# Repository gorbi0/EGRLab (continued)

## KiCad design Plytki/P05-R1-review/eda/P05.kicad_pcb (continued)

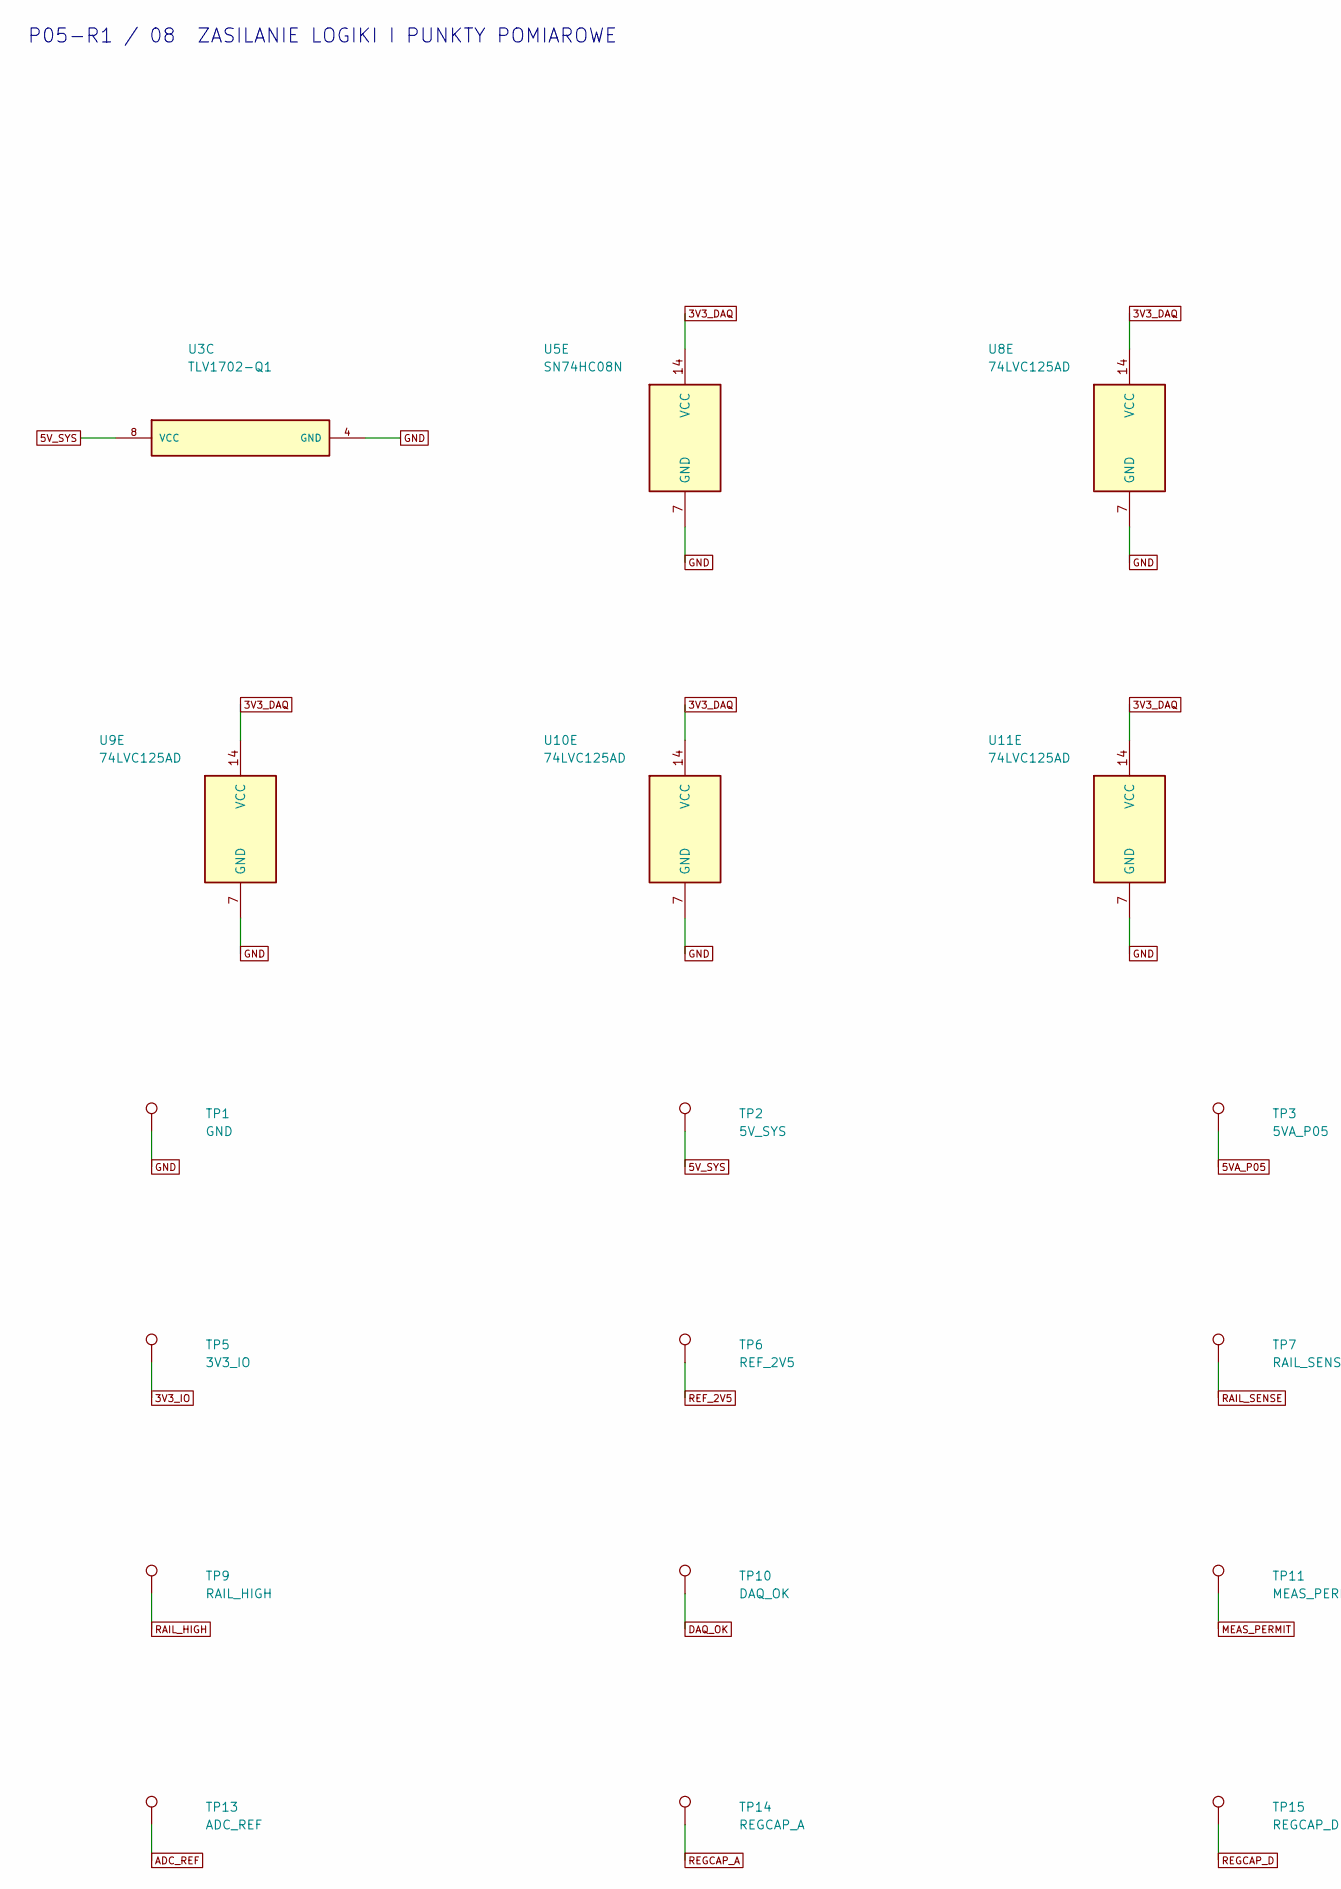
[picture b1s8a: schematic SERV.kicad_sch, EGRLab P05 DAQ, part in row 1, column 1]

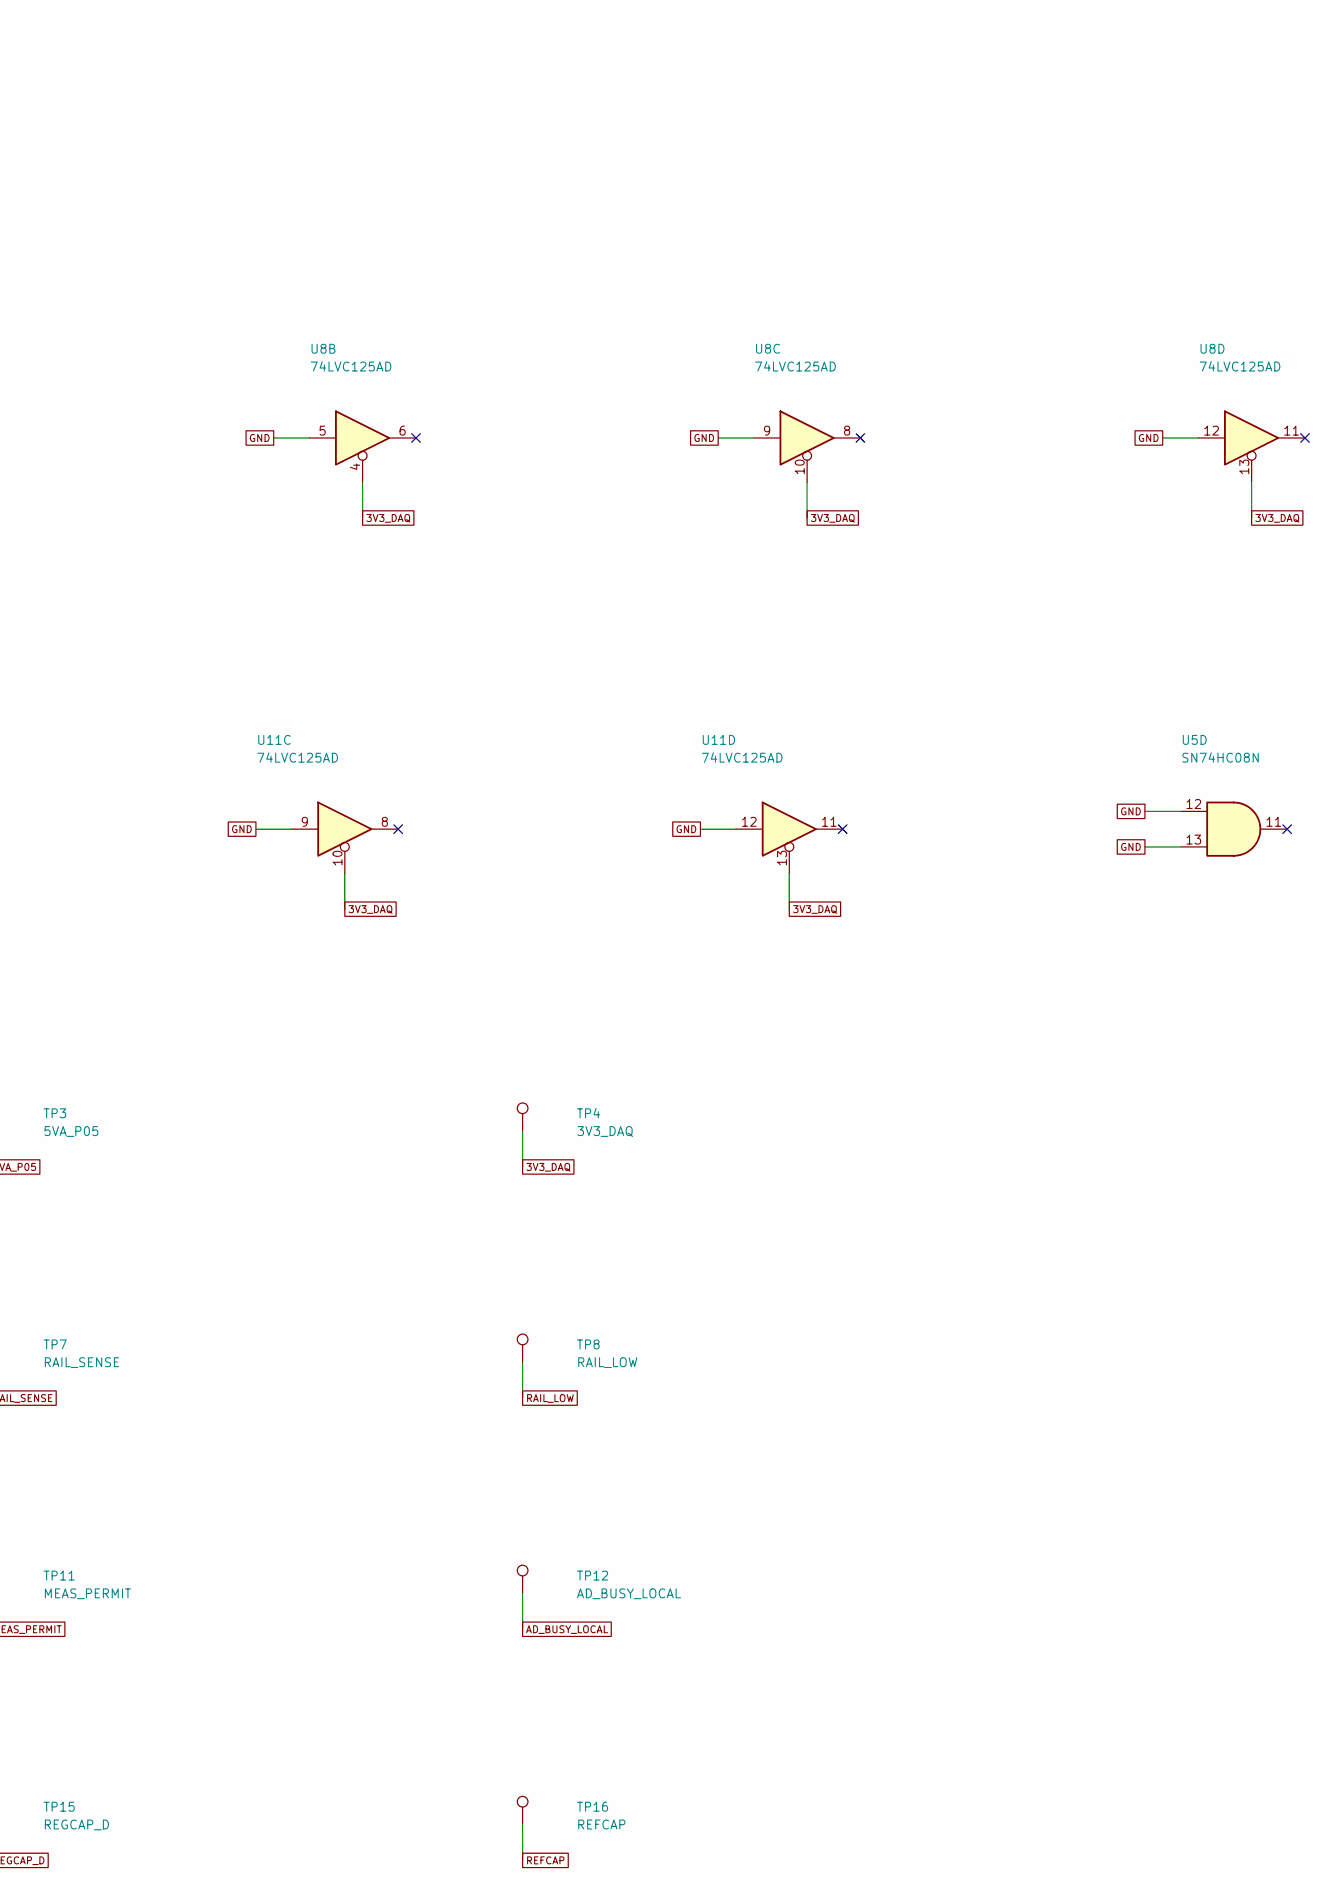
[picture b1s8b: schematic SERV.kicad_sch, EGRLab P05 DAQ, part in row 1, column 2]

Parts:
TP1: GND; TestPad_1; MPN PCB test pad
TP2: 5V_SYS; TestPad_1; MPN PCB test pad
TP3: 5VA_P05; TestPad_1; MPN PCB test pad
TP4: 3V3_DAQ; TestPad_1; MPN PCB test pad
TP5: 3V3_IO; TestPad_1; MPN PCB test pad
TP6: REF_2V5; TestPad_1; MPN PCB test pad
TP7: RAIL_SENSE; TestPad_1; MPN PCB test pad
TP8: RAIL_LOW; TestPad_1; MPN PCB test pad
TP9: RAIL_HIGH; TestPad_1; MPN PCB test pad
TP10: DAQ_OK; TestPad_1; MPN PCB test pad
TP11: MEAS_PERMIT; TestPad_1; MPN PCB test pad
TP12: AD_BUSY_LOCAL; TestPad_1; MPN PCB test pad
TP13: ADC_REF; TestPad_1; MPN PCB test pad
TP14: REGCAP_A; TestPad_1; MPN PCB test pad
TP15: REGCAP_D; TestPad_1; MPN PCB test pad
TP16: REFCAP; TestPad_1; MPN PCB test pad
U3: TLV1702-Q1; VSSOP-8_3x3mm_P0.65mm; MPN TLV1702AQDGKRQ1
U5: SN74HC08N; DIP-14_W7.62mm; MPN SN74HC08N
U8, U9, U10, U11: 74LVC125AD; SOIC-14_3.9x8.7mm_P1.27mm; MPN 74LVC125AD,118

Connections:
3V3_DAQ: TP4.1, U5.14 (VCC), U8.4, U8.10, U8.13, U8.14 (VCC), U9.14 (VCC), U10.14 (VCC), U11.10, U11.13, U11.14 (VCC); also elsewhere on the board
3V3_IO: TP5.1; also elsewhere on the board
5VA_P05: TP3.1; also elsewhere on the board
5V_SYS: TP2.1, U3.8 (VCC); also elsewhere on the board
ADC_REF: TP13.1; also elsewhere on the board
AD_BUSY_LOCAL: TP12.1; also elsewhere on the board
DAQ_OK: TP10.1; also elsewhere on the board
GND: TP1.1, U3.4 (GND), U5.7 (GND), U5.12, U5.13, U8.5, U8.7 (GND), U8.9, U8.12, U9.7 (GND), U10.7 (GND), U11.7 (GND), U11.9, U11.12; also elsewhere on the board
MEAS_PERMIT: TP11.1; also elsewhere on the board
RAIL_HIGH: TP9.1; also elsewhere on the board
RAIL_LOW: TP8.1; also elsewhere on the board
RAIL_SENSE: TP7.1; also elsewhere on the board
REFCAP: TP16.1; also elsewhere on the board
REF_2V5: TP6.1; also elsewhere on the board
REGCAP_A: TP14.1; also elsewhere on the board
REGCAP_D: TP15.1; also elsewhere on the board

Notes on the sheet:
P05-R1 / 08 ZASILANIE LOGIKI I PUNKTY POMIAROWE

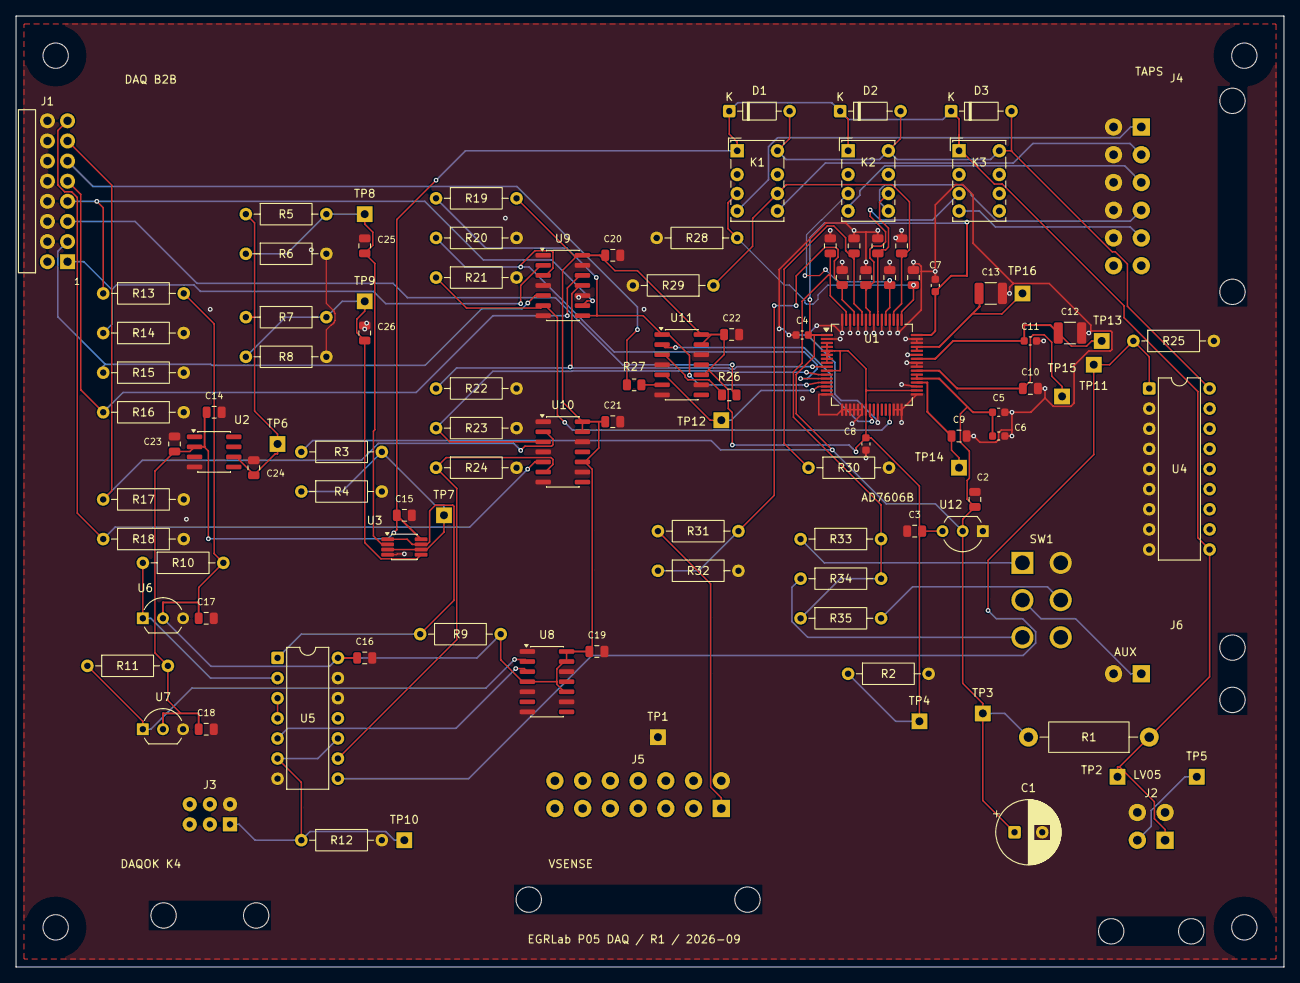
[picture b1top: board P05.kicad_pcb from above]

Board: 2 copper layers, 160.0 x 120.0 mm, 114 parts (0 on the bottom side), 57 nets.

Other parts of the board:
H1, H2, H3, H4: M3 NPTH

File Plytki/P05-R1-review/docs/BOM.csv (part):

ref;source_ref;display;mpn;qty;footprint;on_board;url;note
U1;U1;AD7606BBSTZ;AD7606BBSTZ;1;Package_QFP:LQFP-64_10x10mm_P0.5mm;True;https://www.analog.com/media/en/technical-documentation/data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;"OS=111 serial software; REF_SELECT high = internal reference. Grounded DB pins per serial-mode data sheet."
U2;U13;ADR4525BRZ;ADR4525BRZ;1;Package_SO:SOIC-8_3.9x4.9mm_P1.27mm;True;https://www.analog.com/media/en/technical-documentation/data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;"Reference for rail window only; NOT ADC reference."
U3;U6;TLV1702-Q1;TLV1702AQDGKRQ1;1;Package_SO:VSSOP-8_3x3mm_P0.65mm;True;https://www.ti.com/lit/ds/symlink/tlv1702-q1.pdf;
U4;U18;TBD62083APG;TBD62083APG;1;Package_DIP:DIP-18_W7.62mm;True;https://toshiba.semicon-storage.com/us/semiconductor/product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;COM to coil supply. Inputs 2..8 tied low. Local diodes at coils.
U5;U_READY;SN74HC08N;SN74HC08N;1;Package_DIP:DIP-14_W7.62mm;True;https://www.ti.com/lit/ds/symlink/sn74hc08.pdf;
U6;U_SUP3;MCP120-300DI/TO;MCP120-300DI/TO;1;Package_TO_SOT_THT:TO-92_Inline_Wide;True;https://ww1.microchip.com/downloads/en/DeviceDoc/11184d.pdf;D bondout 1 reset, 2 VDD, 3 GND. Open drain.
U7;U_SUP5;MCP120-450DI/TO;MCP120-450DI/TO;1;Package_TO_SOT_THT:TO-92_Inline_Wide;True;https://ww1.microchip.com/downloads/en/DeviceDoc/11184d.pdf;D bondout 1 reset, 2 VDD, 3 GND. Open drain.
U8;U_SUPBUF;74LVC125AD;74LVC125AD,118;1;Package_SO:SOIC-14_3.9x8.7mm_P1.27mm;True;https://assets.nexperia.com/documents/data-sheet/74LVC125A.pdf;"Nexperia Ioff, soldered directly; no adapter."
U9;U_RX1;74LVC125AD;74LVC125AD,118;1;Package_SO:SOIC-14_3.9x8.7mm_P1.27mm;True;https://assets.nexperia.com/documents/data-sheet/74LVC125A.pdf;"Nexperia Ioff, soldered directly; no adapter."
U10;U_RX2;74LVC125AD;74LVC125AD,118;1;Package_SO:SOIC-14_3.9x8.7mm_P1.27mm;True;https://assets.nexperia.com/documents/data-sheet/74LVC125A.pdf;"Nexperia Ioff, soldered directly; no adapter."
U11;U_TX;74LVC125AD;74LVC125AD,118;1;Package_SO:SOIC-14_3.9x8.7mm_P1.27mm;True;https://assets.nexperia.com/documents/data-sheet/74LVC125A.pdf;"Nexperia Ioff, soldered directly; no adapter."
U12;ADDED_LOCAL_LDO;MCP1700-3302E/TO;MCP1700-3302E/TO;1;Package_TO_SOT_THT:TO-92_Inline_Wide;True;https://ww1.microchip.com/downloads/aemDocuments/documents/A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;Local logic supply derived from ADC AVCC. LV05.3 is test point only.
R1;R_FILT;1R;metal film resistor 1R 1%;1;Resistor_THT:R_Axial_DIN0411_L9.9mm_D3.6mm_P15.24mm_Horizontal;True;;"1W minimum; pulse energy at turn-on >=6mJ. One full-value resistor, no series substitution. Precision parts TCR <=25ppm/K."
C1;C_A;470u / 16V;EEUFR1C471;1;Capacitor_THT:CP_Radial_D8.0mm_P3.50mm;True;;"Panasonic FR, D8 x 11.5mm, pitch 3.5mm; 20%."
C2;ADDED_LDO_IN;1u;X7R 25V 10% 1u;1;Capacitor_SMD:C_0805_2012Metric;True;;
C3;ADDED_LDO_OUT;2.2u;X7R 25V 10% 2.2u;1;Capacitor_SMD:C_0805_2012Metric;True;;
R2;ADDED_LDO_BLEED;1K;metal film resistor 1K 1%;1;Resistor_THT:R_Axial_DIN0207_L6.3mm_D2.5mm_P10.16mm_Horizontal;True;;One full-value resistor, no series substitution. Precision parts TCR <=25ppm/K.
C4;C_DEC_U1_1;100n;X7R 25V 10% 100n;1;Capacitor_SMD:C_0603_1608Metric;True;;
C5;C_DEC_U1_37;100n;X7R 25V 10% 100n;1;Capacitor_SMD:C_0603_1608Metric;True;;
C6;C_DEC_U1_38;100n;X7R 25V 10% 100n;1;Capacitor_SMD:C_0603_1608Metric;True;;
C7;C_DEC_U1_48;100n;X7R 25V 10% 100n;1;Capacitor_SMD:C_0603_1608Metric;True;;
C8;C_DEC_U1_23;100n;X7R 25V 10% 100n;1;Capacitor_SMD:C_0603_1608Metric;True;;
C9;C_REGCAP_A;1u;X7R 25V 10% 1u;1;Capacitor_SMD:C_0805_2012Metric;True;;
C10;C_REGCAP_D;1u;X7R 25V 10% 1u;1;Capacitor_SMD:C_0805_2012Metric;True;;
C11;C_ADC_REF;100n;X7R 25V 10% 100n;1;Capacitor_SMD:C_0603_1608Metric;True;;
C12;ADDED_INTERNAL_REF_BULK;22u;C3225X7R1E226M250AB;1;Capacitor_SMD:C_1210_3225Metric;True;https://product.tdk.com/en/search/capacitor/ceramic/mlcc/inf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;22uF 25V X7R 20%, 1210. Ceff >=10uF including bias/tolerance/temperature: procurement acceptance, not yet measured.
C13;C_REFCAP;22u;C3225X7R1E226M250AB;1;Capacitor_SMD:C_1210_3225Metric;True;https://product.tdk.com/en/search/capacitor/ceramic/mlcc/inf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;22uF 25V X7R 20%, 1210. Ceff >=10uF including bias/tolerance/temperature: procurement acceptance, not yet measured.
C14;C_DEC_U2;100n;X7R 25V 10% 100n;1;Capacitor_SMD:C_0805_2012Metric;True;;
C15;C_DEC_U3;100n;X7R 25V 10% 100n;1;Capacitor_SMD:C_0805_2012Metric;True;;
C16;C_DEC_U5;100n;X7R 25V 10% 100n;1;Capacitor_SMD:C_0805_2012Metric;True;;
C17;C_DEC_U6;100n;X7R 25V 10% 100n;1;Capacitor_SMD:C_0805_2012Metric;True;;
C18;C_DEC_U7;100n;X7R 25V 10% 100n;1;Capacitor_SMD:C_0805_2012Metric;True;;
C19;C_DEC_U8;100n;X7R 25V 10% 100n;1;Capacitor_SMD:C_0805_2012Metric;True;;
C20;C_DEC_U9;100n;X7R 25V 10% 100n;1;Capacitor_SMD:C_0805_2012Metric;True;;
C21;C_DEC_U10;100n;X7R 25V 10% 100n;1;Capacitor_SMD:C_0805_2012Metric;True;;
C22;C_DEC_U11;100n;X7R 25V 10% 100n;1;Capacitor_SMD:C_0805_2012Metric;True;;
C23;C_REF_IN;1u;X7R 25V 10% 1u;1;Capacitor_SMD:C_0805_2012Metric;True;;
C24;C_REF_OUT;1u;X7R 25V 10% 1u;1;Capacitor_SMD:C_0805_2012Metric;True;;
C25;C_RAIL_LOW;10n;X7R 25V 10% 10n;1;Capacitor_SMD:C_0805_2012Metric;True;;
C26;C_RAIL_HIGH;10n;X7R 25V 10% 10n;1;Capacitor_SMD:C_0805_2012Metric;True;;
R3;R_RAIL_T;15K;MBB0207 precision metal film 15K 0.1%;1;Resistor_THT:R_Axial_DIN0207_L6.3mm_D2.5mm_P10.16mm_Horizontal;True;;One full-value resistor, no series substitution. Precision parts TCR <=25ppm/K.
R4;R_RAIL_B;10K;MBB0207 precision metal film 10K 0.1%;1;Resistor_THT:R_Axial_DIN0207_L6.3mm_D2.5mm_P10.16mm_Horizontal;True;;One full-value resistor, no series substitution. Precision parts TCR <=25ppm/K.
R5;R_RAIL_LT;5.90K;MBB0207 precision metal film 5.90K 0.1%;1;Resistor_THT:R_Axial_DIN0207_L6.3mm_D2.5mm_P10.16mm_Horizontal;True;;One full-value resistor, no series substitution. Precision parts TCR <=25ppm/K.
R6;R_RAIL_LB;20K;MBB0207 precision metal film 20K 0.1%;1;Resistor_THT:R_Axial_DIN0207_L6.3mm_D2.5mm_P10.16mm_Horizontal;True;;One full-value resistor, no series substitution. Precision parts TCR <=25ppm/K.
R7;R_RAIL_HT;5.23K;MBB0207 precision metal film 5.23K 0.1%;1;Resistor_THT:R_Axial_DIN0207_L6.3mm_D2.5mm_P10.16mm_Horizontal;True;;One full-value resistor, no series substitution. Precision parts TCR <=25ppm/K.
R8;R_RAIL_HB;24.9K;MBB0207 precision metal film 24.9K 0.1%;1;Resistor_THT:R_Axial_DIN0207_L6.3mm_D2.5mm_P10.16mm_Horizontal;True;;One full-value resistor, no series substitution. Precision parts TCR <=25ppm/K.
R9;R_RAIL_PULL;10K;metal film resistor 10K 1%;1;Resistor_THT:R_Axial_DIN0207_L6.3mm_D2.5mm_P10.16mm_Horizontal;True;;One full-value resistor, no series substitution. Precision parts TCR <=25ppm/K.
R10;R_U_SUP3;10K;metal film resistor 10K 1%;1;Resistor_THT:R_Axial_DIN0207_L6.3mm_D2.5mm_P10.16mm_Horizontal;True;;One full-value resistor, no series substitution. Precision parts TCR <=25ppm/K.
R11;R_SUP5_RAW;10K;metal film resistor 10K 1%;1;Resistor_THT:R_Axial_DIN0207_L6.3mm_D2.5mm_P10.16mm_Horizontal;True;;One full-value resistor, no series substitution. Precision parts TCR <=25ppm/K.
R12;R_READY_PD;10K;metal film resistor 10K 1%;1;Resistor_THT:R_Axial_DIN0207_L6.3mm_D2.5mm_P10.16mm_Horizontal;True;;One full-value resistor, no series substitution. Precision parts TCR <=25ppm/K.
R13;R_EXT_ADC_CS;10K;metal film resistor 10K 1%;1;Resistor_THT:R_Axial_DIN0207_L6.3mm_D2.5mm_P10.16mm_Horizontal;True;;One full-value resistor, no series substitution. Precision parts TCR <=25ppm/K.
R14;R_EXT_ADC_SCLK;10K;metal film resistor 10K 1%;1;Resistor_THT:R_Axial_DIN0207_L6.3mm_D2.5mm_P10.16mm_Horizontal;True;;One full-value resistor, no series substitution. Precision parts TCR <=25ppm/K.
R15;R_EXT_ADC_SDI;10K;metal film resistor 10K 1%;1;Resistor_THT:R_Axial_DIN0207_L6.3mm_D2.5mm_P10.16mm_Horizontal;True;;One full-value resistor, no series substitution. Precision parts TCR <=25ppm/K.
R16;R_EXT_ADC_CONVST;10K;metal film resistor 10K 1%;1;Resistor_THT:R_Axial_DIN0207_L6.3mm_D2.5mm_P10.16mm_Horizontal;True;;One full-value resistor, no series substitution. Precision parts TCR <=25ppm/K.
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
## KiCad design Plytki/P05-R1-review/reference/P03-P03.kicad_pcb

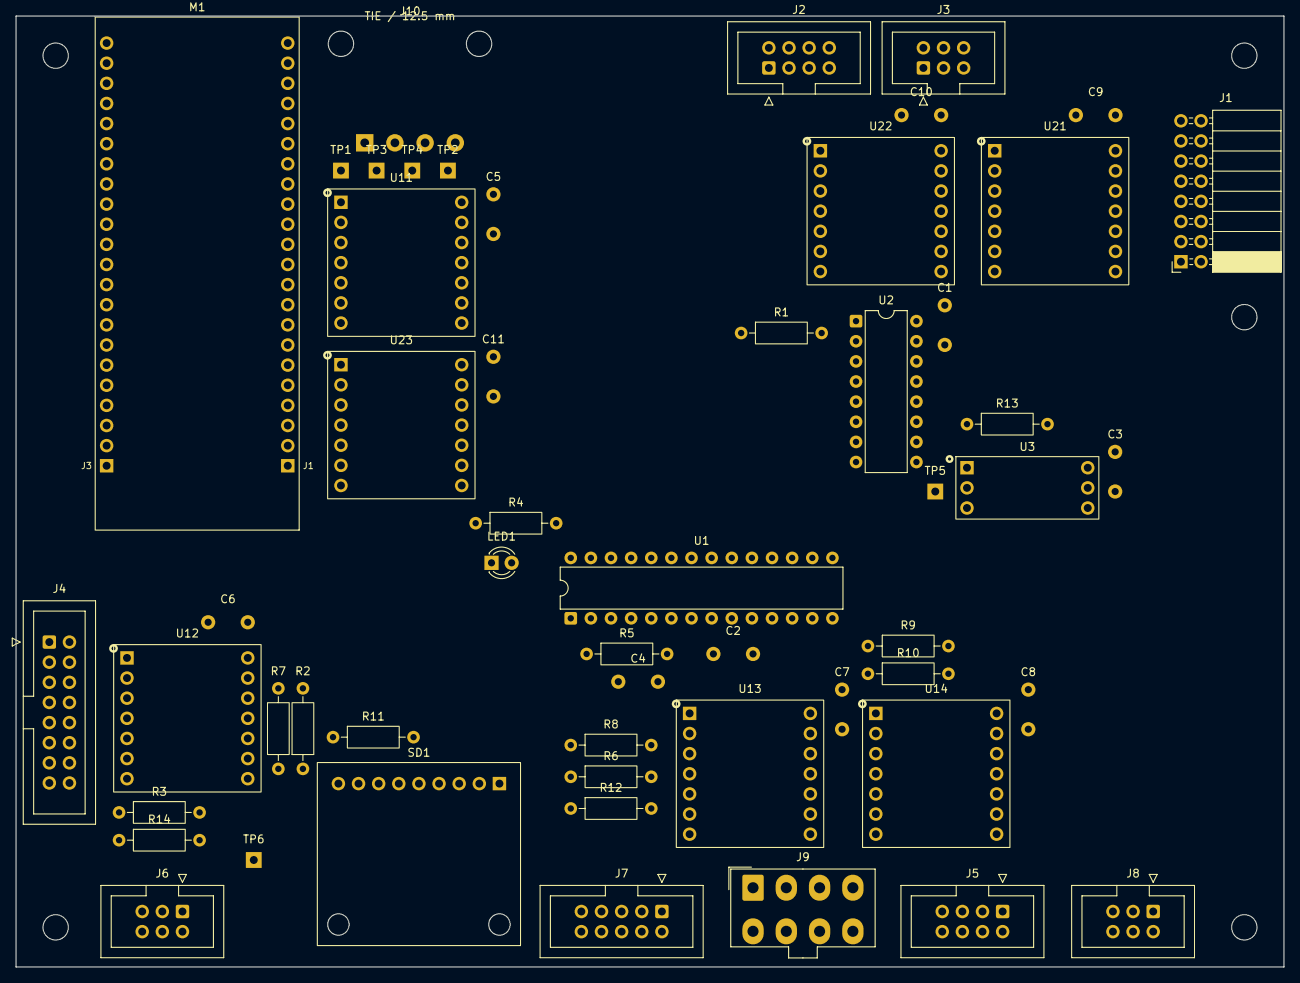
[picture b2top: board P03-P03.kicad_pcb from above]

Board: 2 copper layers, 160.0 x 120.0 mm, 59 parts (0 on the bottom side), 73 nets, no tracks yet.

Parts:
C1, C2, C3, C4, C5, C6, C7, C8, C9, C10, C11: 100nF / X7R; C_Vishay_K15_H5_P5
H1, H2, H3, H4, H5: M3 NPTH
J1: DAQ B2B / RA socket 2x8; PinSocket_2x08_P2.54mm_Horizontal
J2: ILOG / IDC 2x4 KEY 2; IDC-Header_2x04_P2.54mm_Vertical
J3: ITEST / IDC 2x3 KEY 2; IDC-Header_2x03_P2.54mm_Vertical
J4: SAFE / IDC 2x8 KEY 4; IDC-Header_2x08_P2.54mm_Vertical
J5: DIR / IDC 2x4 KEY 4; IDC-Header_2x04_P2.54mm_Vertical
J6: SFAULT / IDC 2x3 KEY 3; IDC-Header_2x03_P2.54mm_Vertical
J7: TEMP / IDC 2x5 KEY 4; IDC-Header_2x05_P2.54mm_Vertical
J8: CAN / IDC 2x3 KEY 4; IDC-Header_2x03_P2.54mm_Vertical
J9: PANELCORE / Mini-Fit Jr 8p; Molex_Mini-Fit_Jr_5566-08A_2x04_P4.20mm_Vertical
J10: LV03 / soldered harness; Pigtail_LV_4xAWG22_P3.81
LED1: GREEN 3mm / STATUS; LED_D3.0mm
M1: Waveshare ESP32-S3-DEV-KIT-N32R16V; Waveshare_ESP32-S3-DEV-KIT_2x22_W22.86
R1, R2, R3, R5, R6, R7, R8, R11, R13: 10K / 1%; R_Axial_DIN0207_L6.3mm_D2.5mm_P10.16mm_Horizontal
R4: 1K / 1%; R_Axial_DIN0207_L6.3mm_D2.5mm_P10.16mm_Horizontal
R9, R10: 4K7 / 1%; R_Axial_DIN0207_L6.3mm_D2.5mm_P10.16mm_Horizontal
R12: 330R / 1%; R_Axial_DIN0207_L6.3mm_D2.5mm_P10.16mm_Horizontal
R14: 0R; R_Axial_DIN0207_L6.3mm_D2.5mm_P10.16mm_Horizontal
SD1: Adafruit 4682 microSD (3V); Adafruit_4682_microSD_1x09
TP1: 5V_SYS; TestPad_1
TP2: 3V3_CORE; TestPad_1
TP3: 3V3_IO; TestPad_1
TP4, TP6: GND; TestPad_1
TP5: SUP_N; TestPad_1
U1: MCP23017-E/SP; DIP-28_W7.62mm
U2: SN74HC139N; DIP-16_W7.62mm
U3: TPS3808G33DBVR / PA0085; Adapter_SOT23-6_DIP6_W15.24_ChipQuik_PA0085
U11, U12, U13, U14, U21, U22, U23: 74LVC125A / SO14 adapter; Adapter_SO14_DIP14_W15.24_Kamami575068

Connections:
3V3_CORE: C1.1, C2.1, C3.1, C5.1, C6.1, C7.1, C8.1, C9.1, C10.1, C11.1, M1.J1-1, M1.J1-2, R1.2, R5.1, R9.1, R10.1, R11.1, R13.2, R14.1, SD1.1, TP2.1, U1.9, U2.15, U2.16, U3.3, U3.5, U3.6, U11.14, U12.14, U13.14, U14.14, U21.14, U22.14, U23.14
3V3_IO: J10.3, TP3.1, U14.4, U14.10, U14.13
/5V_SYS: J10.1, M1.J1-21, TP1.1
/CURRENT_CS_N: M1.J3-10, R1.1, U2.1
/I2C_SCL: M1.J1-8, R9.2, U1.12
/I2C_SDA: M1.J1-16, R10.2, U1.13
/IO/ADC_BUSY: J1.11, U11.5
/IO/ADC_CONVST: J1.9, U21.11
/IO/ADC_CS: J1.7, U21.3
/IO/ADC_DOUTA: J1.5, J2.3, J3.3, U11.2
/IO/ADC_RESET: J1.13, U22.3
/IO/ADC_SCLK: J1.1, J2.1, J3.1, U21.6
/IO/ADC_SDI: J1.3, U21.8
/IO/CAN_RX: J8.3, U11.12
/IO/CS_ILOG_N: J2.5, U22.8
/IO/CS_ITEST_N: J3.5, U22.11
/IO/ENA_DIAG: J5.5, U13.2
/IO/ENB_DIAG: J5.7, U13.5
/IO/HW_ARMED: J4.7, R3.1, U12.2
/IO/INTERLOCK: J4.9, U12.5
/IO/LOGGER_CLEAR: J9.4, R6.1, U13.9
/IO/LOGGER_CURRENT_OK: J2.7, R2.1, U12.9
/IO/MEAS_EN: J1.15, U22.6
/IO/SENSOR_HEALTHY: J6.1, R7.1, U12.12
/IO/TC1_CS: J7.7, U23.8
/IO/TC2_CS: J7.9, U23.11
/IO/TEST_KEY: J9.3, U14.2
/IO/TEST_PRESENT: J9.5, R8.1, U13.12
/LED_A: LED1.2, R4.2
/MEAS_BANK: U1.23, U2.2
/SCOPE_TRIG: M1.J3-7, R12.1
/SD_CS: M1.J1-7, R11.2, SD1.6
/STATUS_LED: R4.1, U1.28
ADC_BUSY_CORE: M1.J1-20, U11.6
ADC_CONVST_SRC: M1.J1-19, U21.12
ADC_CS_SRC: M1.J1-18, U21.2
ADC_DOUTA_CORE: M1.J1-17, U11.3
ADC_RESET_SRC: U1.21, U22.2
ADC_SCLK_SRC: M1.J1-15, U21.5
ADC_SDI_SRC: M1.J3-5, U21.9
CAN_RX_CORE: M1.J1-11, U11.11
CAN_TX: J8.1, M1.J1-10
CORE_LINK: J4.13, R14.2
CS_ILOG_N_SRC: U2.4, U22.9
CS_ITEST_N_SRC: U2.5, U22.12
ENA_DIAG_CORE: U1.3, U13.3
ENB_DIAG_CORE: U1.4, U13.6
GND: C1.2, C2.2, C3.2, C4.2, C5.2, C6.2, C7.2, C8.2, C9.2, C10.2, C11.2, J1.4, J1.6, J1.8, J1.10, J1.12, J1.14, J1.16, J2.4, J2.6, J2.8, J3.4, J3.6, J4.2, J4.6, J4.8, J4.10, J4.12, J4.14, J4.16, J5.2, J5.6, J5.8, J6.2, J7.2, J7.6, J7.8, J7.10, J8.2, J9.1, J9.8, J10.2, J10.4, LED1.1, M1.J1-22, M1.J3-1, M1.J3-21, M1.J3-22, R2.2, R3.2, R6.2, R7.2, R8.2, SD1.2, TP4.1, TP6.1, U1.10, U1.15, U1.16, U1.17, U2.3, U2.8, U2.13, U2.14, U3.2, U11.1, U11.4, U11.7, U11.10, U11.13, U12.1, U12.4, U12.7, U12.10, U12.13, U13.1, U13.4, U13.7, U13.10, U13.13, U14.1, U14.5, U14.7, U14.9, U14.12, U21.1, U21.4, U21.7, U21.10, U21.13, U22.1, U22.4, U22.7, U22.10, U22.13, U23.1, U23.4, U23.7, U23.10, U23.13
HEARTBEAT: J4.3, M1.J3-18
HW_ARMED_CORE: M1.J3-8, U12.3
INTERLOCK_CORE: M1.J3-6, U12.6
LOGGER_CLEAR_CORE: U1.5, U13.8
LOGGER_CURRENT_OK_CORE: U1.25, U12.8
MARK: C4.1, J9.2, R5.2, U1.7
MCU_ARM: J4.5, M1.J3-9
MEAS_EN_SRC: U1.22, U22.5
MOTOR_INA: J5.1, U1.26
MOTOR_INB: J5.3, U1.27
N_J_SCOPE_HOT: J9.7, R12.2
PWM: J4.1, M1.J3-4
SENSOR_ENABLE: J4.11, U1.24
SENSOR_HEALTHY_CORE: U1.2, U12.11
SPI3_MISO: J7.5, SD1.4, U11.9
SPI3_MISO_CORE: M1.J1-6, U11.8
SPI3_MOSI: J7.3, SD1.5, U23.6
SPI3_MOSI_SRC: M1.J1-5, U23.5
SPI3_SCLK: J7.1, SD1.3, U23.3
SPI3_SCLK_SRC: M1.J1-4, U23.2
SUP_N: J4.15, R13.1, TP5.1, U1.18, U3.1
TC1_CS_SRC: M1.J1-12, U23.9
TC2_CS_SRC: M1.J1-9, U23.12
TEST_KEY_CORE: U1.1, U14.3
TEST_PRESENT_CORE: U1.6, U13.11
